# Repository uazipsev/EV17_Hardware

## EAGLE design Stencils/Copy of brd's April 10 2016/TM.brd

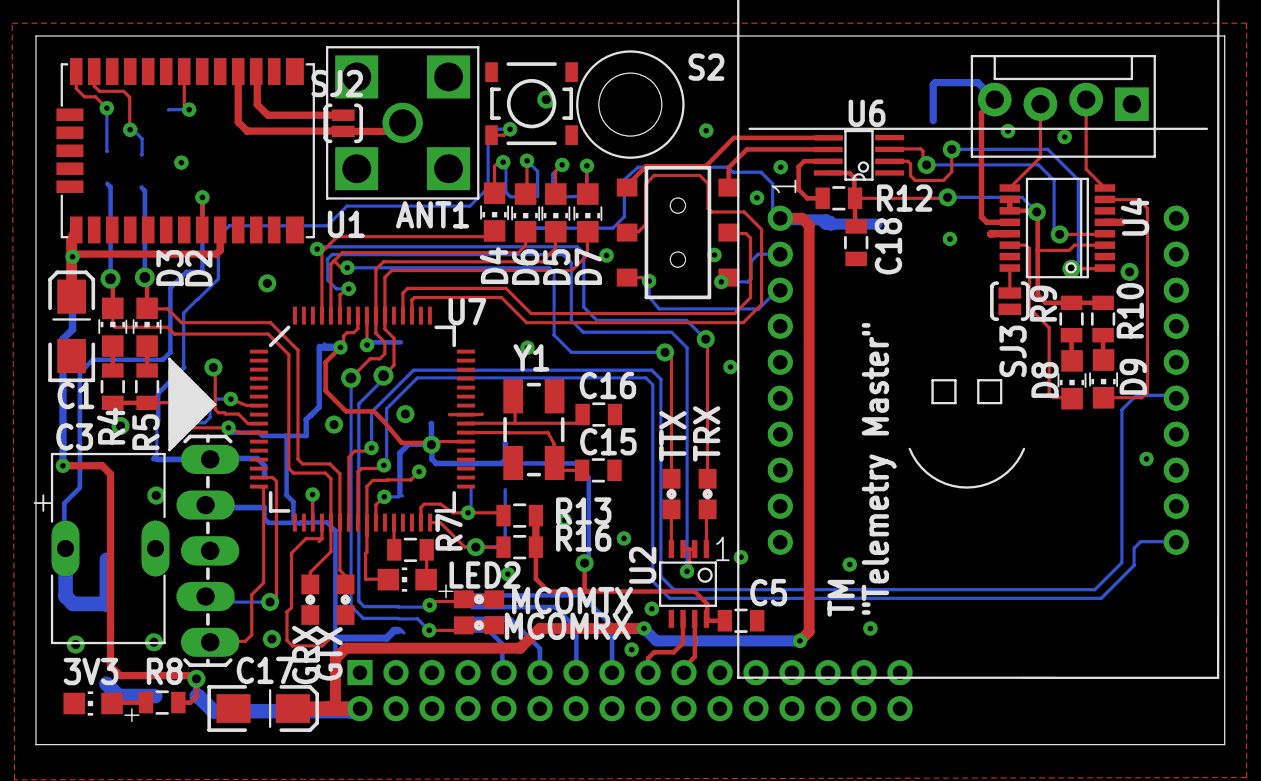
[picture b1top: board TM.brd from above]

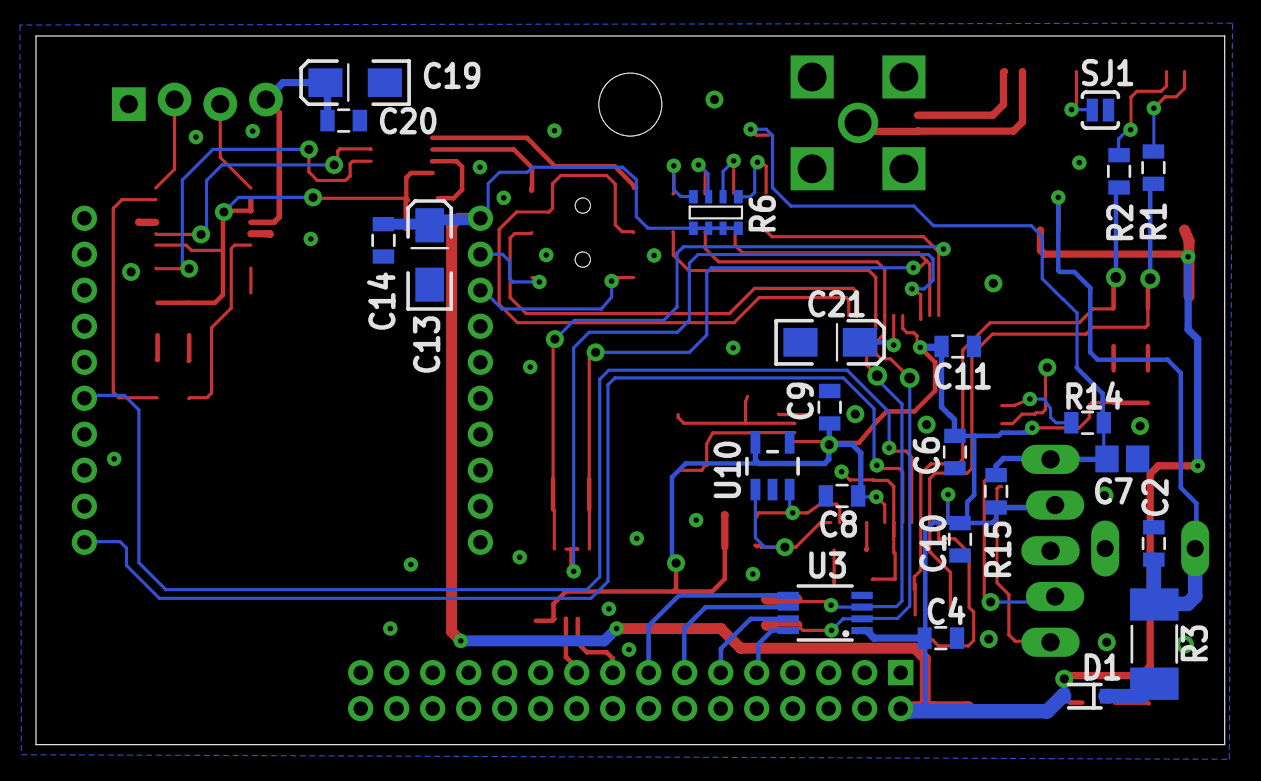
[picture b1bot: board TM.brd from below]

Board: 2 copper layers, 66.0 x 39.4 mm, 71 parts (23 on the bottom side), 60 nets.

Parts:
3V3: CHIP-LED0805
ANT1: CONMCX002; CONSMA002
C1, C13, C17, C19, C21: 10UF; EIA3216-16V
C2, C14: 1UF; 0805
C3: 220MF; EEC-S0HD224V
C4, C5, C6, C8, C9, C10, C11, C18, C20: 0.1UF; 0805
C7: 10n; C0805
C15, C16: 12PF; 0805
CARD1: CARD-2016CARD; CARD-2016
D1: BAS316-TP; SOD-323
D2, D6, D7, D9: GREEN; CHIP_LED0805
D3, D4, D5, D8: RED; CHIP_LED0805
GRX: TP; 0603
GTX: TP; 0603
ICSP: ICSP; 1X05_LOCK_LONGPADS
JP13: MOLEX-1X4_LOCK
LED2: CHIP-LED0805
MCOMRX: TP; 0603
MCOMTX: TP; 0603
R1, R2: 220; 0805
R3: 50; R2010
R4, R5, R9, R10, R12, R15: 1K; 0805
R6: RN-4_1K; MNR14
R7, R8, R14: 499; 0805
R13, R16: 2K; 0805
S1: DPDT; AYZ0202
S2: ts; TACTILE_SWITCH_SMD-2
SJ1, SJ2: NO; SJ_2S-NO
SJ3: PAD-JUMPER-2-NO_YES_SILK
TRX: TP; 0603
TTX: TP; 0603
U1: CAM-M8Q
U2: SN75HVD08DRMSOP; MSOP-8
U3: ISL83077MSOP; MSOP8
U4: FT230X; SSOP-16
U5: RM024; RM024-TH
U6: SN74LVC2G241; VFSOP-8
U7: DSPIC33EP256GM306; TQFP-64
U10: 24LC00T-I/OT; SOT23-5
U$3: INDPK1; PICKIT-PIN-1
Y1: 12Mhz; CRYSTAL-SMD-5X3

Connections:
3V: C18.1, R9.2, R10.2, R12.2, U4.3, U4.10, U4.11, U6.8
+3V3: C1.A, C4.1, C5.1, C6.1, C8.1, C9.1, C10.1, C11.1, C13.A, C14.1, C17.A, CARD1.2, D1.2, ICSP.2, R4.2, R5.2, R6.5, R6.6, R6.7, R6.8, R8.2, R13.2, R15.2, R16.2, U1.1, U1.9, U2.8, U3.1, U5.1, U7.10, U7.19, U7.26, U7.38, U7.57, U10.5
CONNECTED: U5.15, U7.23
GND: 3V3.C, ANT1.1, ANT1.2, ANT1.3, ANT1.4, C1.C, C2.2, C3.-, C4.2, C5.2, C6.2, C7.2, C8.2, C9.2, C10.2, C11.2, C13.C, C14.2, C15.2, C16.2, C17.C, C18.2, C19.C, C20.2, C21.C, CARD1.32, ICSP.3, JP13.1, LED2.C, S2.2, SJ1.1, SJ3.1, U1.4, U1.5, U1.10, U1.11, U1.12, U1.13, U1.14, U1.15, U1.18, U1.19, U1.21, U1.22, U1.27, U1.31, U2.5, U3.4, U4.5, U4.13, U5.10, U6.1, U6.4, U7.9, U7.20, U7.25, U7.41, U10.2
GPS-RX: D3.C, GRX.1, GRX.2, R1.2, U7.21
GPS-TX: D2.C, GTX.1, GTX.2, R2.2, U7.22
unnamed: D2.A, R5.1
unnamed: R2.1, U1.25
unnamed: ANT1.C, SJ2.2, U1.17
unnamed: R1.1, U1.26
unnamed: SJ1.2, U1.20
unnamed: D1.1, R3.2
unnamed: 3V3.A, R8.1
unnamed: C2.1, C3.+, R3.1, U1.8
unnamed: D7.A, R6.4
unnamed: D5.A, R6.3
unnamed: R7.2, U7.28
unnamed: C16.1, U7.40, Y1.3
unnamed: C15.1, U7.39, Y1.1
unnamed: LED2.A, R7.1
unnamed: R13.1, U7.31, U10.3
unnamed: SJ2.1, U1.16
unnamed: D9.A, R10.1
unnamed: D9.C, U4.7
unnamed: D8.C, U4.14
unnamed: U4.4, U6.3
unnamed: D4.A, R6.1
unnamed: D6.A, R6.2
unnamed: D3.A, R4.1
unnamed: SJ3.2, U4.16
unnamed: U4.1, U6.2
unnamed: JP13.3, U4.9
unnamed: D8.A, R9.1
unnamed: R16.1, U7.32, U10.1
unnamed: JP13.2, U4.8
unnamed: R12.1, U6.7
unnamed: C19.A, C20.1, JP13.4, U4.12
unnamed: C7.1, ICSP.1, R14.1, R15.1, S2.1
unnamed: R14.2, U7.7
unnamed: C21.A, U7.56
unnamed: ICSP.4, U7.15
unnamed: ICSP.5, U7.16
RS-ECU-A: CARD1.9, U3.8
RS-ECU-B: CARD1.11, U3.7
RS-ECU-Y: CARD1.15, U3.5
RS-ECU-Z: CARD1.13, U3.6
RX: S1.2, U7.52
RXD0: D4.C, TRX.1, TRX.2, U2.1, U7.61
RXD2: D5.C, MCOMRX.1, MCOMRX.2, U3.2, U7.55
RXD3: S1.1, U6.6
RXD4: S1.3, U5.2
SETUP: U5.11, U7.24
TSA: CARD1.17, U2.6
TSB: CARD1.19, U2.7
TX: S1.5, U7.51
TXD0: D6.C, TTX.1, TTX.2, U2.4, U7.60
TXD2: D7.C, MCOMTX.1, MCOMTX.2, U3.3, U7.54
TXD3: S1.4, U6.5
TXD4: S1.6, U5.3
U3-EN: U2.2, U2.3, U7.59

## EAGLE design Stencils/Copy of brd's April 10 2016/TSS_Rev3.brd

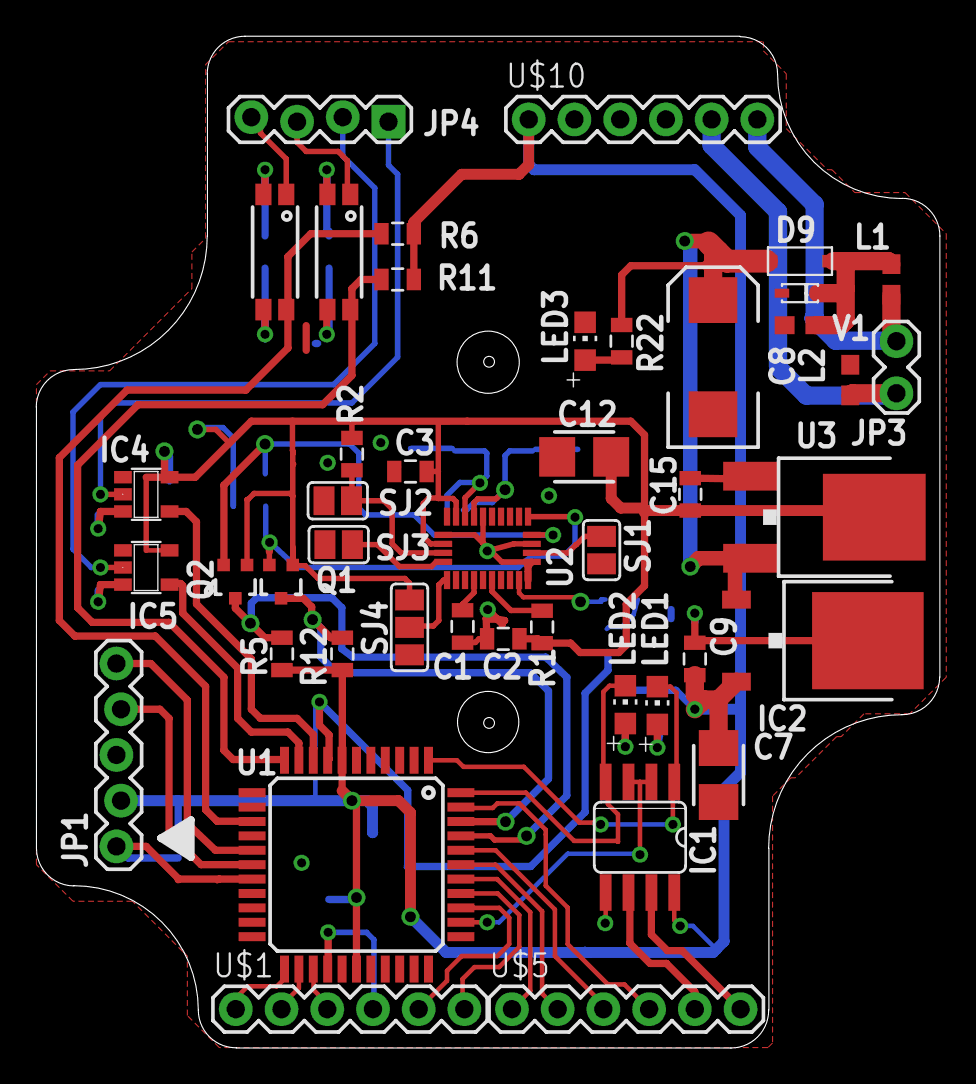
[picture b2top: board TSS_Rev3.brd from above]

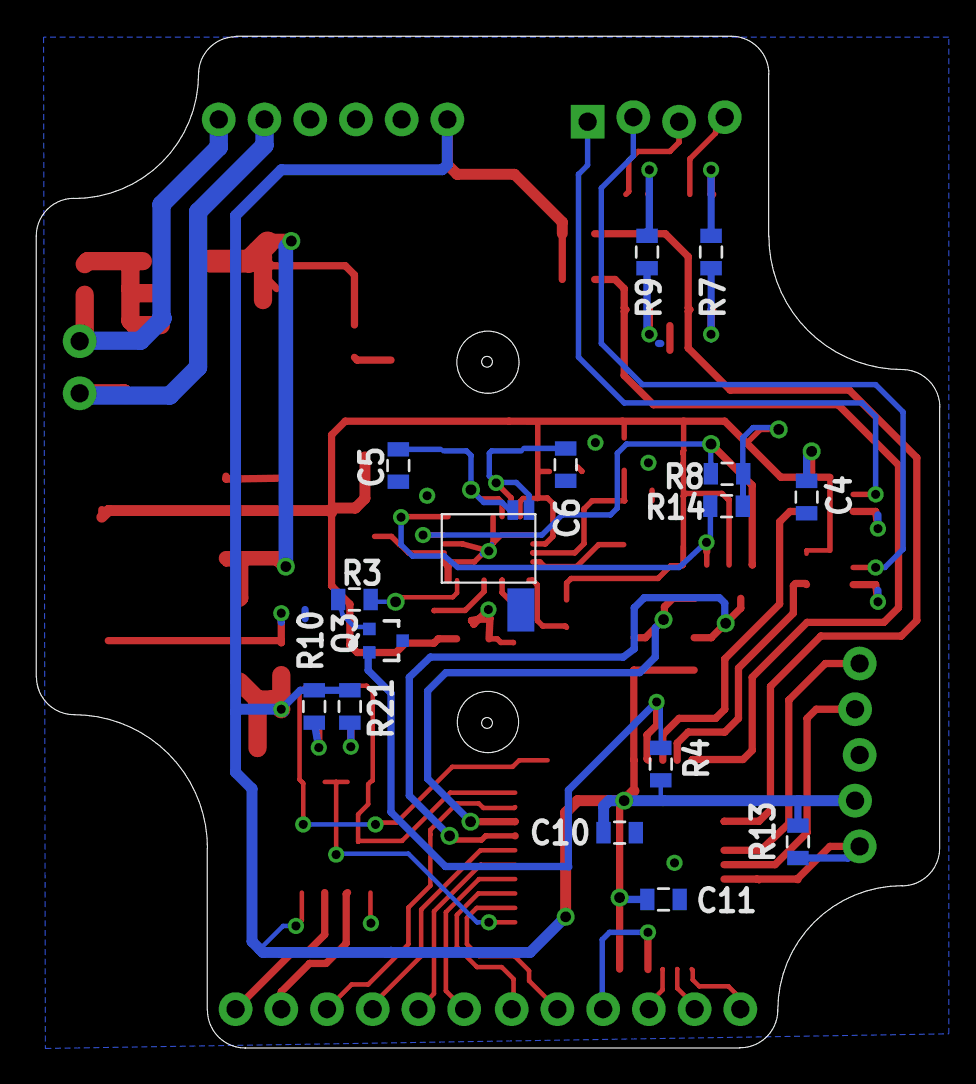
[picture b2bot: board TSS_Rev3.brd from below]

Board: 2 copper layers, 50.2 x 56.2 mm, 60 parts (16 on the bottom side), 53 nets.

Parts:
C1, C4: 100nF; 0805
C2: 6.8nF; 0805
C3: 120nF; 0805
C5, C6: 22pF; 0805
C7, C12: CT3528
C8: EIA7343
C9, C10, C11, C15: 0.1uF; 0805
D9: SOD-123
D10: MM5Z30; SOD-523F
IC1: MAX481CSA; SO08
IC2: 7805DT; TO252
IC4, IC5: 74AUC1G17DBV; SOT23-5
JP1: 1X05_LOCK
JP3: M02LOCK; 1X02_LOCK
JP4: 1X04_LOCK
L1, L2: FB; 0603
LED1, LED2, LED3: CHIP-LED0805
Q1, Q2, Q3: MOSFET-NCHANNEL2N7002PW; SOT323
R1, R2, R5, R6, R8, R11, R12, R13, R14: 10k; 0805
R3, R4, R10, R21: 1k; 0805
R7, R9: 2.2k; 0805
R22: 2.4k; 0805
SJ1, SJ2, SJ3: SJ
SJ4: SJ_2
U1: PIC18F45K22; TQFP-44
U2: BOSCH_IMUSURFACEMOUNT; LGA_28
U3: NCP1117DT; DPAK
U$1, U$5, U$10: 6X.1; 1X06
U$2, U$4: TCMT1103-OPTO; SSOP-4
U$3: AB26TRQ; 3PAD_CAN
V1: 30Vdc; 0603

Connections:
5V: C7.+, C9.1, C10.1, C11.1, IC1.8, IC2.2, JP1.2, R4.1, R5.2, R6.2, R10.1, R11.2, R12.2, R13.2, R21.1, U1.7, U1.28, U$10.P$1
9V: C8.A, D9.C, IC2.1, R22.1, U3.3
+3V3: C2.1, C3.1, C4.1, C12.+, C15.1, IC4.5, IC5.5, Q1.1, Q2.1, R1.2, R2.2, R8.2, R14.2, SJ4.1, U2.P$3, U2.P$28, U3.2
+9: JP3.2, L1.1, U$10.P$6
-: JP3.1, L2.1, U$10.P$5
AIN1: U1.36, U$1.P$5
AIN2: U1.37, U$1.P$6
AIN3: U1.38, U$5.P$1
AIN4: U1.39, U$5.P$2
AIN5: U1.40, U$5.P$3
AIN6: U1.43, U$5.P$4
COM_EN: IC1.2, IC1.3, U1.35
DIN1: U1.23, U$1.P$1
DIN2: U1.24, U$1.P$2
DIN3: U1.25, U$1.P$3
DIN4: U1.26, U$1.P$4
GHT: D9.A, D10.C, L1.2, V1.2
GND: C1.2, C2.2, C3.2, C4.2, C5.2, C6.2, C7.-, C8.C, C9.2, C10.2, C11.2, C12.-, C15.2, D10.A, IC1.5, IC2.3, IC4.3, IC5.3, JP1.3, L2.2, LED3.C, Q3.3, R7.1, R9.1, SJ1.1, SJ2.1, SJ3.1, SJ4.3, U1.6, U1.29, U2.P$2, U2.P$15, U2.P$16, U2.P$18, U2.P$25, U3.1, U$2.3, U$4.3, V1.1
INT_PIC: Q3.2, R4.2, U1.8
MCLR: JP1.1, R13.1, U1.18
unnamed: SJ3.2, U2.P$5
unnamed: R2.1, SJ2.2, U2.P$4
unnamed: SJ4.2, U2.P$6
unnamed: LED3.A, R22.2
unnamed: LED1.A, R10.2
unnamed: LED2.A, R21.2
unnamed: C6.1, U2.P$27, U$3.2
unnamed: C5.1, U2.P$26, U$3.1
unnamed: R7.2, U$2.2
unnamed: SJ1.2, U2.P$17
unnamed: R9.2, U$4.2
unnamed: R3.2, U2.P$14
unnamed: C1.1, U2.P$9
unnamed: R1.1, U2.P$11
unnamed: Q3.1, R3.1
PGC: JP1.5, U1.16
PGD: JP1.4, U1.17
PWM_RTR1: IC4.4, U1.9
PWM_RTR2: IC5.4, U1.10
PWM_RTR_TMP1: IC4.2, JP4.1
PWM_RTR_TMP2: IC5.2, JP4.2
RS485-A: IC1.6, U$5.P$5
RS485-B: IC1.7, U$5.P$6
RX: IC1.1, LED1.C, U1.1
SCL_3V: Q2.2, R8.1, U2.P$19
SCL_5V: Q2.3, R5.1, U1.41
SDA_3V: Q1.2, R14.1, U2.P$20
SDA_5V: Q1.3, R12.1, U1.42
SPD1: R11.1, U1.11, U$4.4
SPD2: R6.1, U1.14, U$2.4
SPEED_1: JP4.4, U$2.1
SPEED_2: JP4.3, U$4.1
TX: IC1.4, LED2.C, U1.44

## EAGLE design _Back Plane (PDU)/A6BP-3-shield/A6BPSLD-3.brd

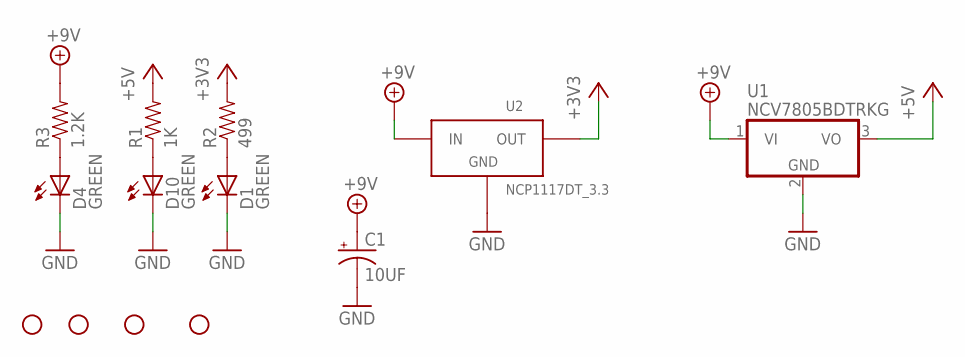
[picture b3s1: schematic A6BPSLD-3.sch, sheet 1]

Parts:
C1: 10UF; EIA3216-16V
D1, D4, D10: GREEN; CHIP_LED0805
R1: 1K; 0805
R2: 499; 0805
R3: 1.2K; 0805
STANDOFF2, STANDOFF6, STANDOFF7, STANDOFF8: STAND-OFF
U1: NCV7805BDTRKG; DPAK
U2: NCP1117DT_3.3; DPAK

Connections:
+3V3: R2.2, U2.2 (OUT); also elsewhere on the board
+5V: R1.2, U1.3 (VO); also elsewhere on the board
+9V: C1.A (+), R3.2, U1.1 (VI), U2.3 (IN); also elsewhere on the board
GND: C1.C (-), D1.C, D4.C, D10.C, U1.2 (GND), U2.1 (GND); also elsewhere on the board
unnamed: D4.A, R3.1
unnamed: D1.A, R2.1
unnamed: D10.A, R1.1

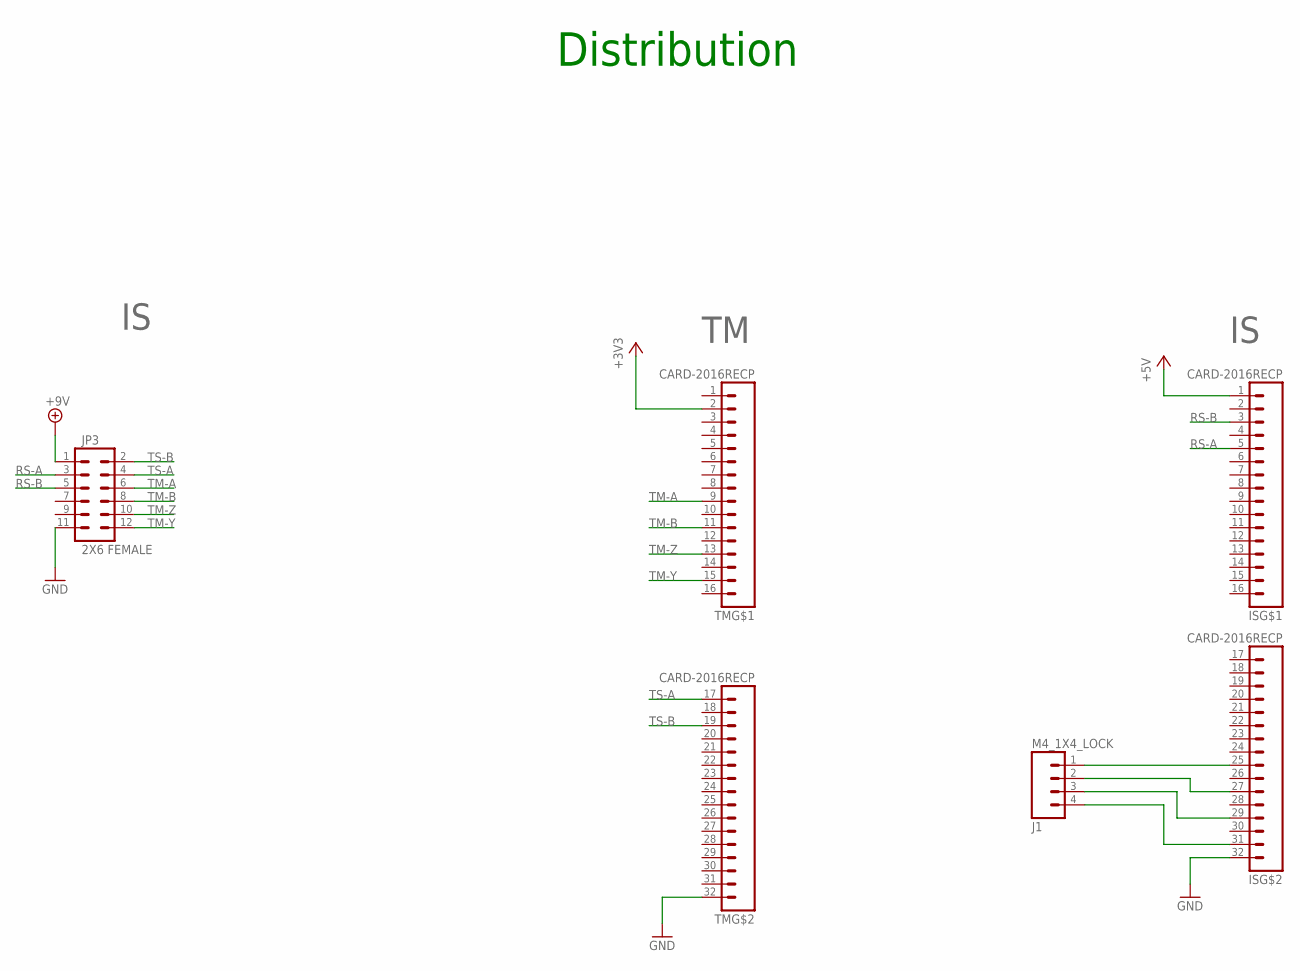
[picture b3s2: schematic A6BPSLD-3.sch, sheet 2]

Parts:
IS: CARD-2016RECP; CARD-2016-RCP
J1: M4_1X4_LOCK; MOLEX_1X4
JP3: 2X6 FEMALE; 2X6
TM: CARD-2016RECP; CARD-2016-RCP

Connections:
+3V3: TM.2; also elsewhere on the board
+5V: IS.1; also elsewhere on the board
+9V: JP3.1; also elsewhere on the board
GND: IS.32 (16), JP3.11, TM.32 (16); also elsewhere on the board
unnamed: IS.25 (9), J1.1
unnamed: IS.27 (11), J1.2
unnamed: IS.29 (13), J1.3
unnamed: IS.31 (15), J1.4
RS-A: IS.5, JP3.3
RS-B: IS.3, JP3.5
TM-A: JP3.6, TM.9
TM-B: JP3.8, TM.11
TM-Y: JP3.12, TM.15
TM-Z: JP3.10, TM.13
TS-A: JP3.4, TM.17 (1)
TS-B: JP3.2, TM.19 (3)

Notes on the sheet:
Distribution

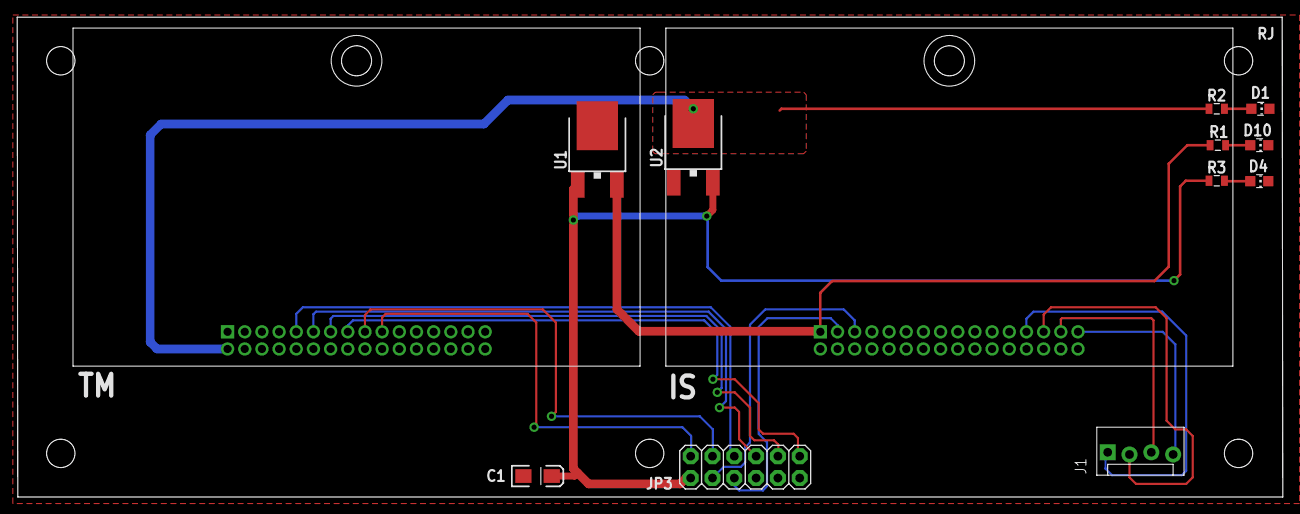
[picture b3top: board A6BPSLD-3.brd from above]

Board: 2 copper layers, 147.4 x 55.9 mm, 19 parts (0 on the bottom side), 19 nets.

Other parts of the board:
STANDOFF1, STANDOFF4: STAND-OFF

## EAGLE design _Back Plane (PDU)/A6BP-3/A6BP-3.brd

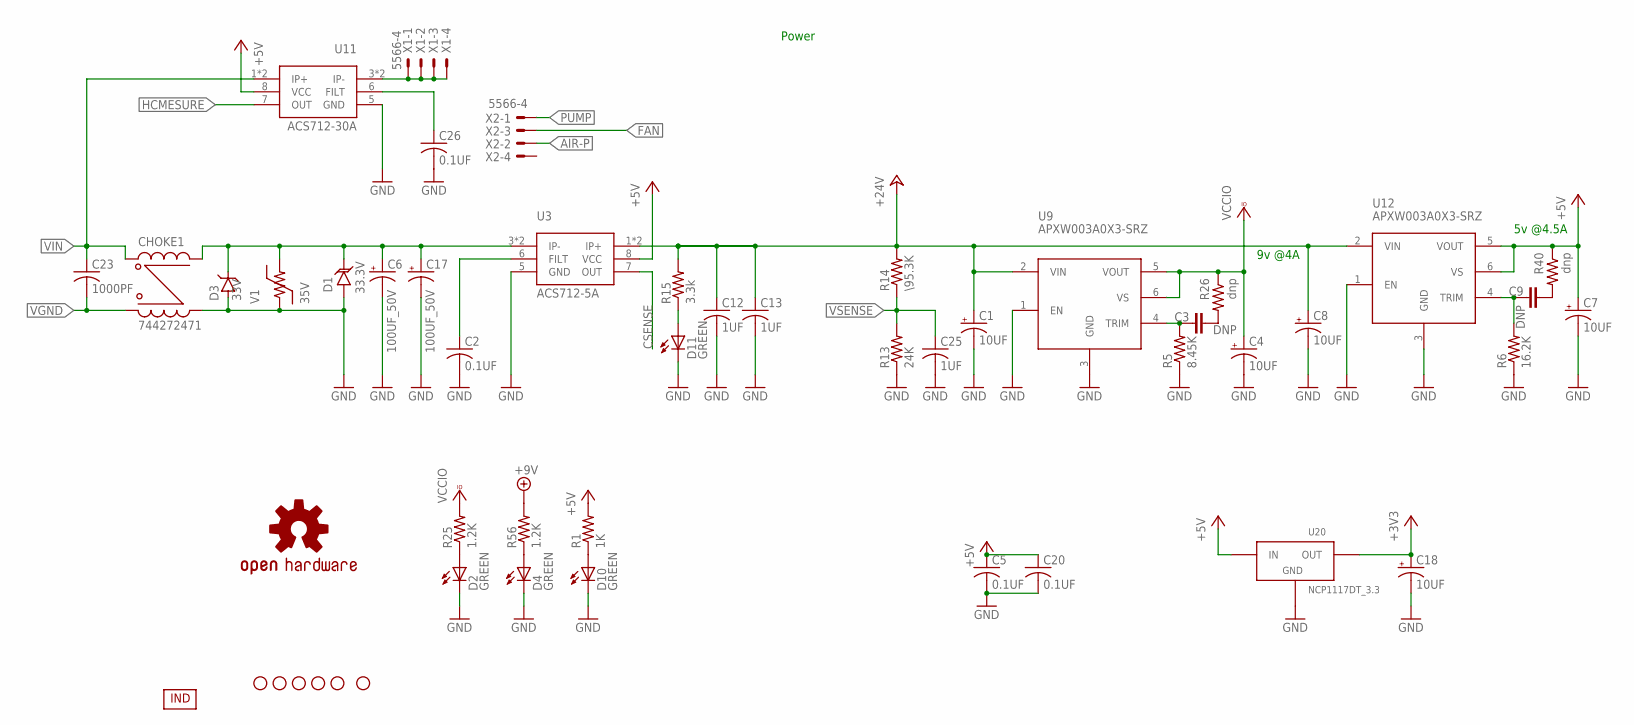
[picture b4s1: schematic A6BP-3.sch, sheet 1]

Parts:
C1, C8: 10UF; EIA7343
C2, C5, C20, C26: 0.1UF; 0805
C3, C9: DNP; 0805
C4, C7, C18: 10UF; EIA3216-16V
C6, C17: 100UF_50V; PANASONIC-G
C12, C13: 1UF; 1206@1
C23: 1000PF; C1825
C25: 1UF; 0805
CHOKE1: 744272471
D1: 33.3V; SMA
D2, D4, D10, D11: GREEN; CHIP_LED0805
D3: 33V; SMB
R1: 1K; 0805
R5: 8.45K; 0805
R6: 16.2K; 0805
R13: 24K; 0805
R14: \95.3K; 0805
R15: 3.3k; 0805
R25, R56: 1.2K; 0805
R26, R40: dnp; R0805
STANDOFF2, STANDOFF3, STANDOFF5, STANDOFF6, STANDOFF7, STANDOFF8: STAND-OFF
U3: ACS712-5A; SO-8
U9, U12: APXW003A0X3-SRZ
U11: ACS712-30A; SO-8
U20: NCP1117DT_3.3; DPAK
U$8: OSHW-LOGOM; OSHW-LOGO-M
U$9: INDPK1; PICKIT-PIN-1
V1: 35V; 0805
X1, X2: 5566-4

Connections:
+3V3: C18.A (+), U20.2 (OUT); also elsewhere on the board
+5V: C5.1 (+), C7.A (+), C20.1 (+), R1.2, R40.1, U3.8 (VCC), U11.8 (VCC), U12.5 (VOUT), U12.6 (VS), U20.3 (IN); also elsewhere on the board
+9V: R56.2
+24V: C1.A (+), C8.A (+), C12.1 (+), C13.1 (+), R14.2, R15.2, U3.1 (IP+), U3.2 (IP+), U9.2 (VIN), U12.2 (VIN); also elsewhere on the board
AIR-P: X2.2; also elsewhere on the board
CSENSE: U3.7 (OUT); also elsewhere on the board
FAN: X2.3; also elsewhere on the board
GND: C1.C (-), C2.2 (-), C4.C (-), C5.2 (-), C6.-, C7.C (-), C8.C (-), C12.2 (-), C13.2 (-), C17.-, C18.C (-), C20.2 (-), C25.2 (-), C26.2 (-), CHOKE1.2 (3), D1.A, D2.C, D3.A, D4.C, D10.C, D11.C, R5.1, R6.1, R13.1, U3.5 (GND), U9.1 (EN), U9.3 (GND), U11.5 (GND), U12.1 (EN), U12.3 (GND), U20.1 (GND), V1.1; also elsewhere on the board
HCMESURE: U11.7 (OUT); also elsewhere on the board
unnamed: D2.A, R25.1
unnamed: D4.A, R56.1
unnamed: D10.A, R1.1
unnamed: C2.1 (+), U3.6 (FILT)
unnamed: C6.+, C17.+, CHOKE1.3 (2), D1.C, D3.C, U3.3 (IP-), U3.4 (IP-), V1.2
unnamed: C3.1, R26.2
unnamed: C3.2, R5.2, U9.4 (TRIM)
unnamed: D11.A, R15.1
unnamed: C9.1, R40.2
unnamed: C9.2, R6.2, U12.4 (TRIM)
unnamed: U11.3 (IP-), U11.4 (IP-), X1.1, X1.2, X1.3, X1.4
unnamed: C26.1 (+), U11.6 (FILT)
PUMP: X2.1; also elsewhere on the board
VCCIO: C4.A (+), R25.2, R26.1, U9.5 (VOUT), U9.6 (VS); also elsewhere on the board
VGND: C23.2 (-), CHOKE1.1 (4); also elsewhere on the board
VIN: C23.1 (+), CHOKE1.4 (1), U11.1 (IP+), U11.2 (IP+); also elsewhere on the board
VSENSE: C25.1 (+), R13.2, R14.1; also elsewhere on the board

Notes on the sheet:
9v @4A
5v @4.5A
Power

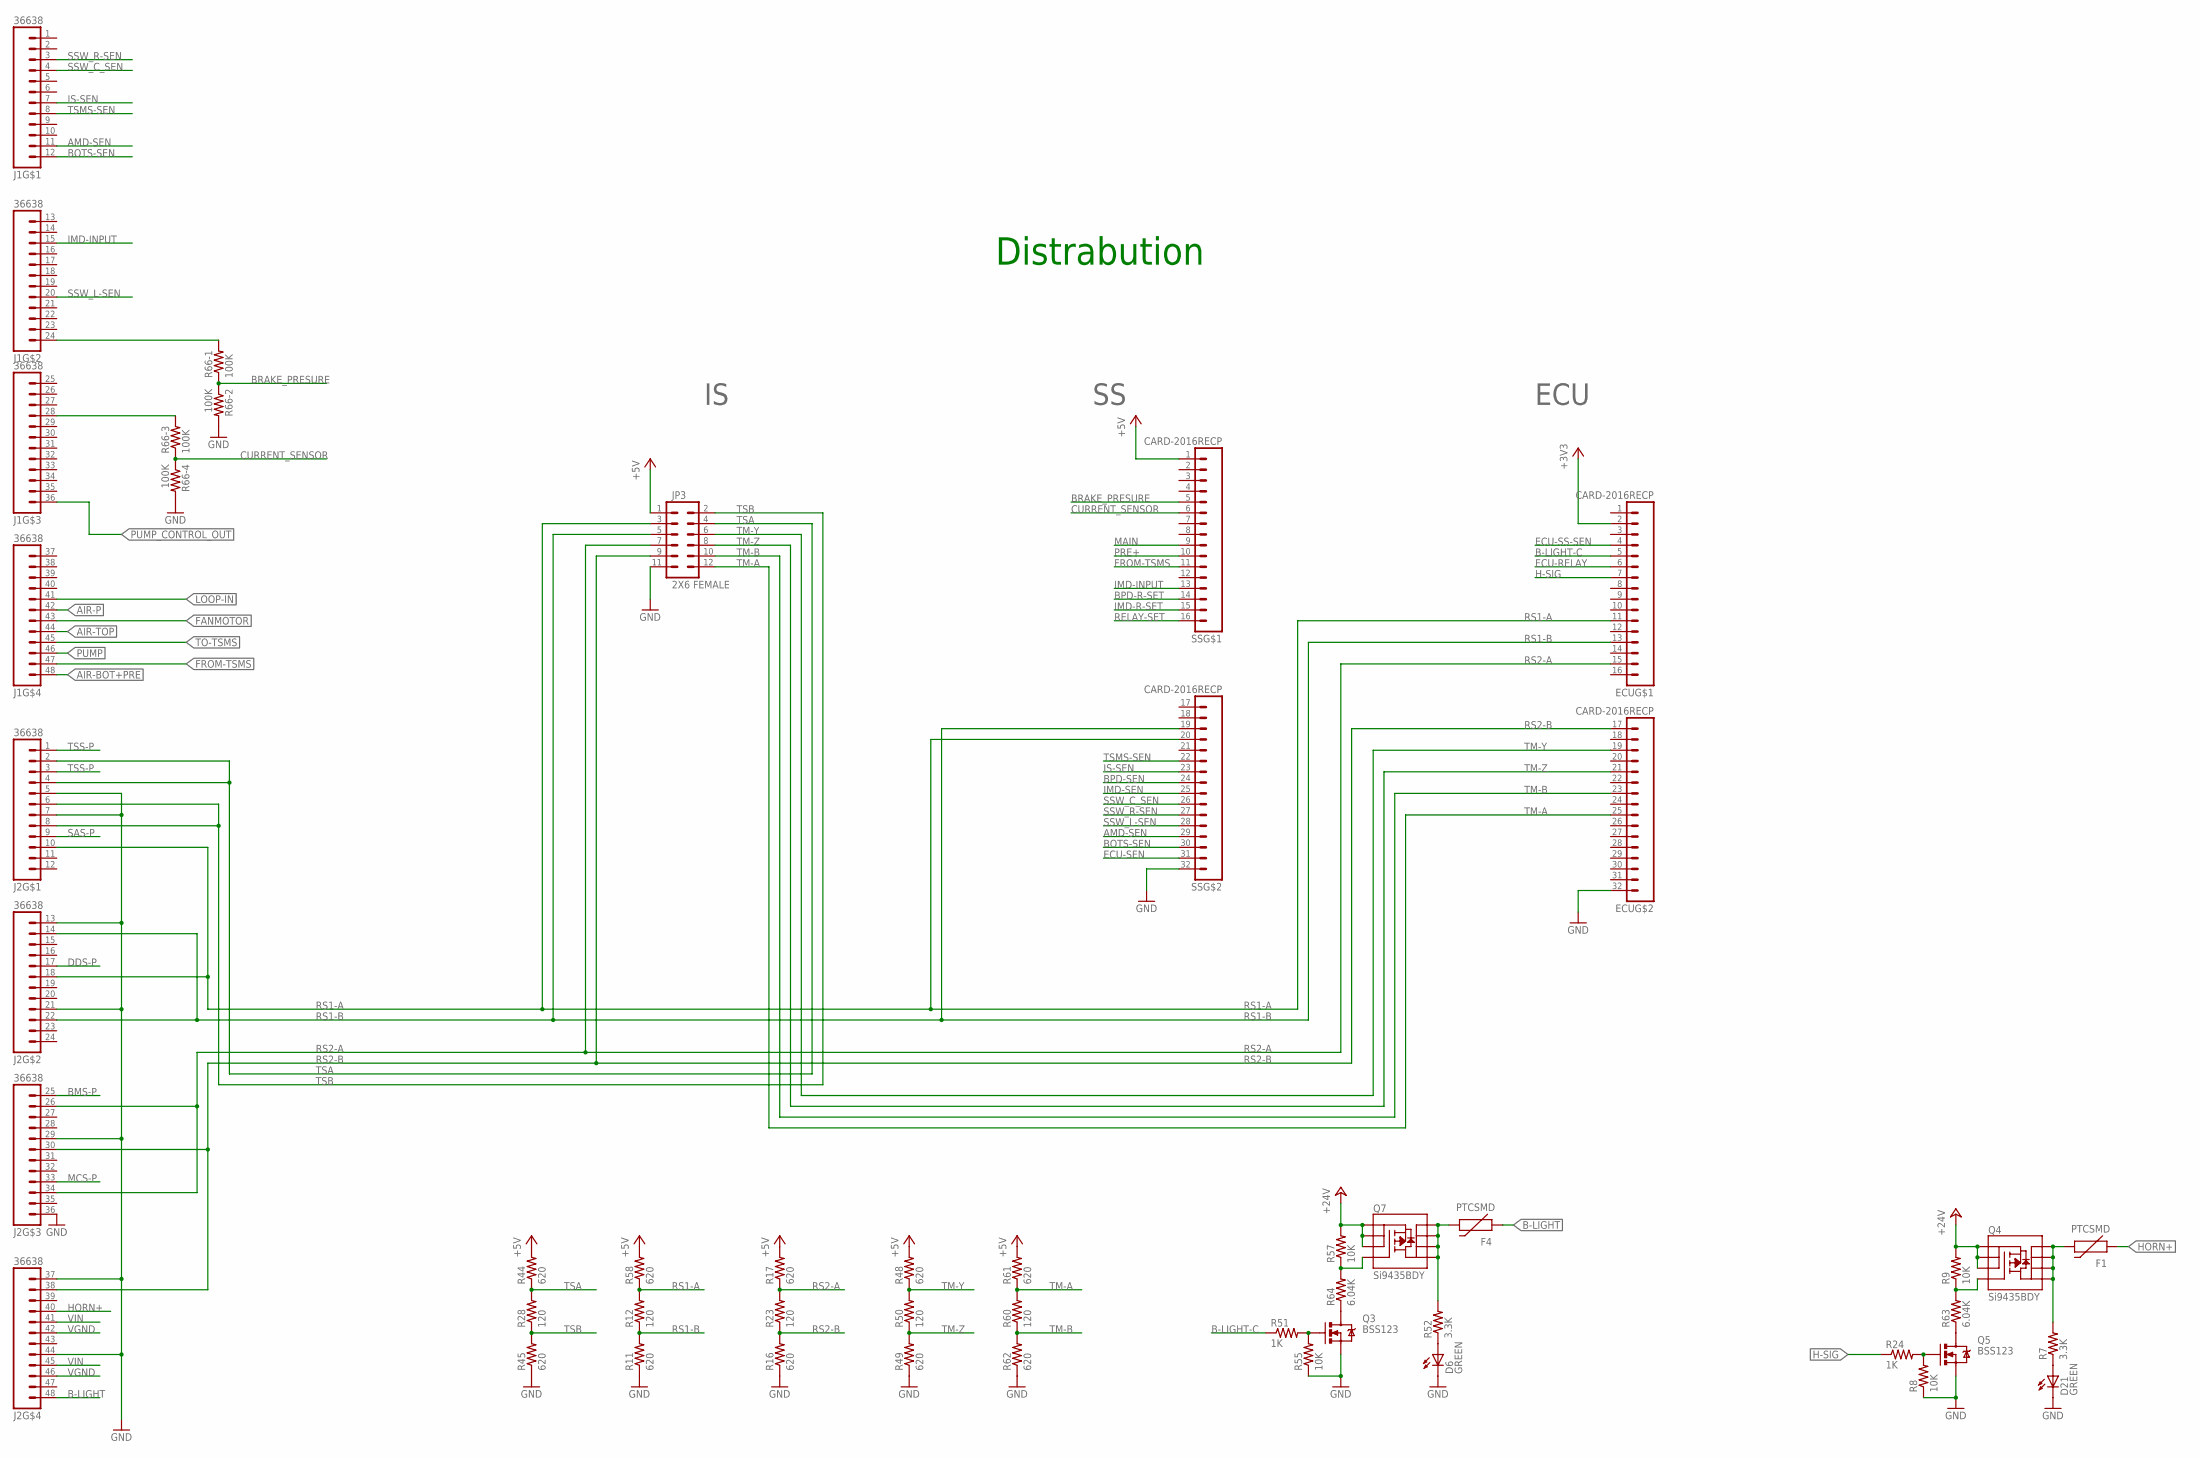
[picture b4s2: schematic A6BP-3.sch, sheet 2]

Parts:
D6, D21: GREEN; CHIP_LED0805
ECU: CARD-2016RECP; CARD-2016-RCP
F1, F4: PTCSMD; PTC-1206
J1, J2: 36638
JP3: 2X6 FEMALE; 2X6
Q3, Q5: BSS123; SOT23
Q4, Q7: Si9435BDY; SO08
R7, R52: 3.3K; 0805
R8, R9, R55, R57: 10K; 0805
R11, R16, R17, R44, R45, R48, R49, R58, R61, R62: 620; 0805
R12, R23, R28, R50, R60: 120; 0805
R24, R51: 1K; 0805
R63, R64: 6.04K; 0805
R66: 100K; MNR14
SS: CARD-2016RECP; CARD-2016-RCP

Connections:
+3V3: ECU.2; also elsewhere on the board
+5V: JP3.1, R17.2, R44.2, R48.2, R58.2, R61.2, SS.1; also elsewhere on the board
+24V: Q4.1 (S), Q4.2 (S), Q4.3 (S), Q7.1 (S), Q7.2 (S), Q7.3 (S), R9.2, R57.2; also elsewhere on the board
AIR-BOT+PRE: J1.48 (12); also elsewhere on the board
AIR-P: J1.42 (6); also elsewhere on the board
AIR-TOP: J1.44 (8); also elsewhere on the board
AMD-SEN: J1.11, SS.29 (13)
B-LIGHT: F4.1, J2.48 (12)
B-LIGHT-C: ECU.5, R51.1
BMS-P: J2.25 (1); also elsewhere on the board
BOTS-SEN: J1.12, SS.30 (14)
BPD-R-SET: SS.14; also elsewhere on the board
BPD-SEN: SS.24 (8); also elsewhere on the board
BRAKE_PRESURE: R66.1, R66.2 (1), SS.5
CURRENT_SENSOR: R66.3 (1), R66.4 (1), SS.6
DDS-P: J2.17 (5); also elsewhere on the board
ECU-RELAY: ECU.6; also elsewhere on the board
ECU-SEN: SS.31 (15); also elsewhere on the board
ECU-SS-SEN: ECU.4
FANMOTOR: J1.43 (7); also elsewhere on the board
FROM-TSMS: J1.47 (11), SS.11; also elsewhere on the board
GND: D6.C, D21.C, ECU.32 (16), J2.5, J2.7, J2.13 (1), J2.21 (9), J2.29 (5), J2.36 (12), J2.37 (1), J2.44 (8), JP3.11, Q3.2 (S), Q5.2 (S), R8.1, R11.1, R16.1, R45.1, R49.1, R55.1, R62.1, R66.5 (2), R66.7 (2), SS.32 (16); also elsewhere on the board
H-SIG: ECU.7, R24.1
HORN+: F1.1, J2.40 (4)
IMD-INPUT: J1.15 (3), SS.13
IMD-R-SET: SS.15; also elsewhere on the board
IMD-SEN: SS.25 (9); also elsewhere on the board
IS-SEN: J1.7, SS.23 (7)
LOOP-IN: J1.41 (5); also elsewhere on the board
MAIN: SS.9; also elsewhere on the board
MCS-P: J2.33 (9); also elsewhere on the board
unnamed: Q4.4 (G), R9.1, R63.2
unnamed: F1.2, Q4.5 (D), Q4.6 (D), Q4.7 (D), Q4.8 (D), R7.2
unnamed: D21.A, R7.1
unnamed: F4.2, Q7.5 (D), Q7.6 (D), Q7.7 (D), Q7.8 (D), R52.2
unnamed: Q7.4 (G), R57.1, R64.2
unnamed: D6.A, R52.1
unnamed: Q5.1 (G), R8.2, R24.2
unnamed: Q5.3 (D), R63.1
unnamed: Q3.3 (D), R64.1
unnamed: J1.24 (12), R66.8 (2)
unnamed: Q3.1 (G), R51.2, R55.2
unnamed: J1.28 (4), R66.6 (2)
PRE+: SS.10; also elsewhere on the board
PUMP: J1.46 (10); also elsewhere on the board
PUMP_CONTROL_OUT: J1.36 (12); also elsewhere on the board
RELAY-SET: SS.16; also elsewhere on the board
RS1-A: ECU.11, J2.10, J2.18 (6), JP3.3, R12.2, R58.1, SS.20 (4)
RS1-B: ECU.13, J2.14 (2), J2.22 (10), JP3.5, R11.2, R12.1, SS.19 (3)
RS2-A: ECU.15, J2.26 (2), J2.34 (10), JP3.7, R17.1, R23.2; also elsewhere on the board
RS2-B: ECU.17 (1), J2.30 (6), J2.38 (2), JP3.9, R16.2, R23.1; also elsewhere on the board
SAS-P: J2.9; also elsewhere on the board
SSW_C_SEN: J1.4, SS.26 (10)
SSW_L-SEN: J1.20 (8), SS.28 (12)
SSW_R-SEN: J1.3, SS.27 (11)
TM-A: ECU.25 (9), JP3.12, R60.2, R61.1
TM-B: ECU.23 (7), JP3.10, R60.1, R62.2
TM-Y: ECU.19 (3), JP3.6, R48.1, R50.2
TM-Z: ECU.21 (5), JP3.8, R49.2, R50.1
TO-TSMS: J1.45 (9); also elsewhere on the board
TSA: J2.2, J2.4, JP3.4, R28.2, R44.1
TSB: J2.6, J2.8, JP3.2, R28.1, R45.2
TSMS-SEN: J1.8, SS.22 (6)
TSS-P: J2.1, J2.3; also elsewhere on the board
VGND: J2.42 (6), J2.46 (10); also elsewhere on the board
VIN: J2.41 (5), J2.45 (9); also elsewhere on the board

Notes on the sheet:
ECU
Distrabution

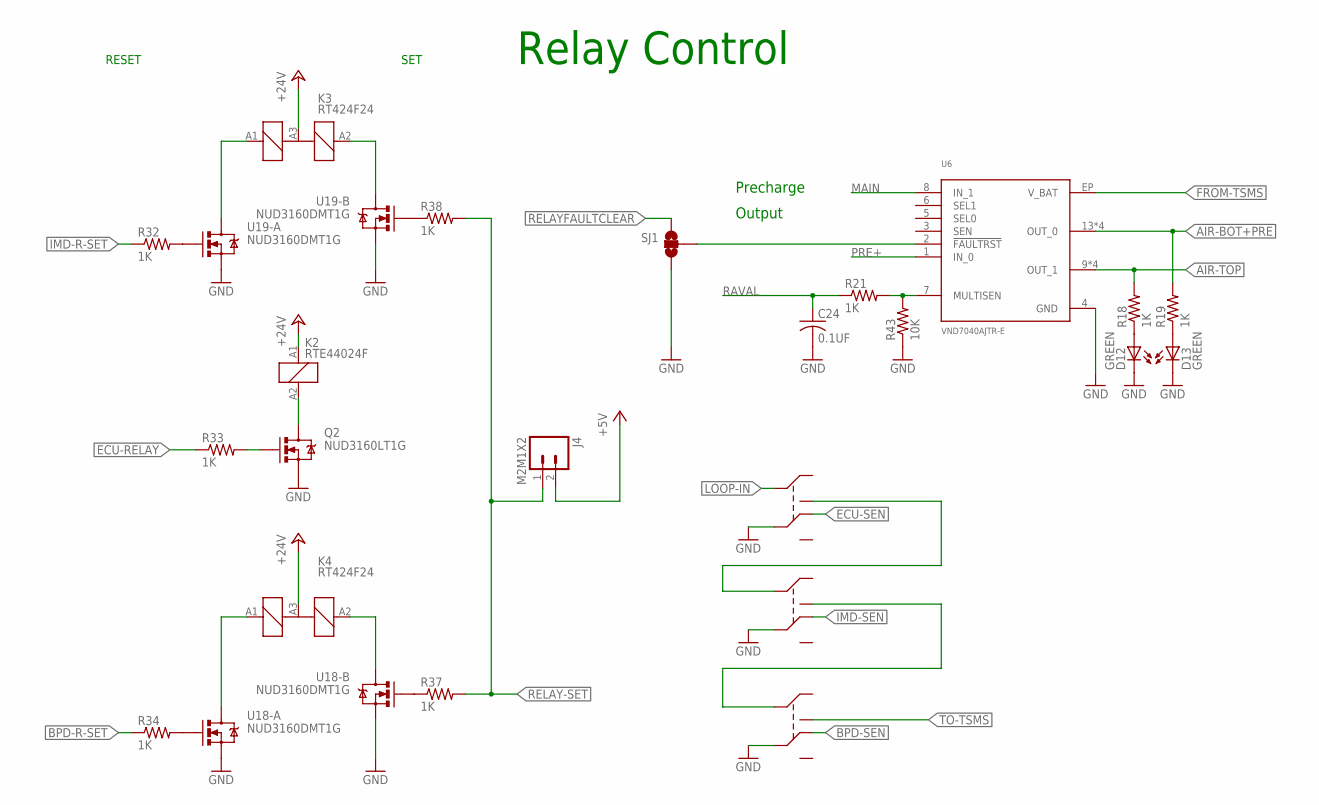
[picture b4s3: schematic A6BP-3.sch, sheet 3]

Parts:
C24: 0.1UF; 0805
D12, D13: GREEN; CHIP_LED0805
J4: M2M1X2; MOLEX-1X2
K2: RTE44024F
K3, K4: RT424F24
Q2: NUD3160LT1G; SOT23
R18, R19, R21, R32, R33, R34, R37, R38: 1K; 0805
R43: 10K; 0805
SJ1: JUMPER-PAD-3-NOFULL_BOX_SILK; PAD-JUMPER-3-NO_YES_SILK_FULL_BOX
U6: VND7040AJTR-E; SSO-16-POWER
U18, U19: NUD3160DMT1G; SC74-6

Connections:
+5V: J4.2; also elsewhere on the board
+24V: K2.A1 (+), K3.A3 (-), K4.A3 (-); also elsewhere on the board
AIR-BOT+PRE: R19.2, U6.13 (OUT_0), U6.14 (OUT_0), U6.15 (OUT_0), U6.16 (OUT_0); also elsewhere on the board
AIR-TOP: R18.2, U6.9 (OUT_1), U6.10 (OUT_1), U6.11 (OUT_1), U6.12 (OUT_1); also elsewhere on the board
BPD-R-SET: R34.1; also elsewhere on the board
BPD-SEN: K4.22 (NC2); also elsewhere on the board
ECU-RELAY: R33.1; also elsewhere on the board
ECU-SEN: K2.22 (NC2); also elsewhere on the board
FROM-TSMS: U6.EP (V_BAT); also elsewhere on the board
GND: C24.2 (-), D12.C, D13.C, K2.21 (C2), K3.21 (C2), K4.21 (C2), Q2.2 (S), R43.1, SJ1.3, U6.4 (GND), U18.1 (S), U18.4 (S), U19.1 (S), U19.4 (S); also elsewhere on the board
IMD-R-SET: R32.1; also elsewhere on the board
IMD-SEN: K3.22 (NC2); also elsewhere on the board
LOOP-IN: K2.11 (C1); also elsewhere on the board
MAIN: U6.8 (IN_1); also elsewhere on the board
unnamed: D12.A, R18.1
unnamed: R34.2, U18.2 (G)
unnamed: K2.14 (NO1), K3.11 (C1)
unnamed: D13.A, R19.1
unnamed: R21.2, R43.2, U6.7 (MULTISEN)
unnamed: SJ1.2, U6.2 (!FAULTRST)
unnamed: K3.14 (NO1), K4.11 (C1)
unnamed: Q2.1 (G), R33.2
unnamed: R38.1, U19.5 (G)
unnamed: K2.A2 (-), Q2.3 (D)
unnamed: K3.A1 (+1), U19.6 (D)
unnamed: R32.2, U19.2 (G)
unnamed: K3.A2 (+2), U19.3 (D)
unnamed: K4.A1 (+1), U18.6 (D)
unnamed: K4.A2 (+2), U18.3 (D)
unnamed: R37.1, U18.5 (G)
PRE+: U6.1 (IN_0); also elsewhere on the board
RAVAL: C24.1 (+), R21.1
RELAY-SET: J4.1, R37.2, R38.2; also elsewhere on the board
RELAYFAULTCLEAR: SJ1.1
TO-TSMS: K4.14 (NO1); also elsewhere on the board

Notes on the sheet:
RESET
SET
Relay Control
Precharge
Output

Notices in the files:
parts and their libraries:
SparkFun-Passives: Licensing: CC v3.0 Share-Alike You are welcome to use this library for commercial purposes.
SparkFun-Passives: Licensing: Creative Commons ShareAlike 4.0 International - https://creativecommons.org/licenses/by-sa/4.0
